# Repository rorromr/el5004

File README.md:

# EL5004: Teleoperación de Go Kart

Desarrollo de un sistema de actuación y teleoperación de un vehículo tipo Go Kart.

Estructura:

```
el5004
|
+-- arduino [Software]
|
+-- doc [Documentación]
|
+-- cad [Archivos CAD]
|
+-- gokart_serial [Interfaz serial con PC]
|
+-- pcb [Diseño PCB]
|
+-- scripts [Scripts de compilación y CI]
```

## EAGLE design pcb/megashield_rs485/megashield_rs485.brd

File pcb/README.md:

# EL5004: Teleoperación de Go Kart

## PCB

El software empleado corresponde [Eagle](http://www.cadsoftusa.com/download-eagle/) (versión >= 7.4).

## Dependencias

* [SparkFun Eagle Libraries](https://github.com/sparkfun/SparkFun-Eagle-Libraries)
* [Librería Eagle Lab. Mecatrónica](https://github.com/mecatronica-fcfm/mecatronica_eagle_lib)

## Componentes principales

* [RS485 Transceiver TI SN75176BP](http://www.ti.com/lit/gpn/sn75176b)

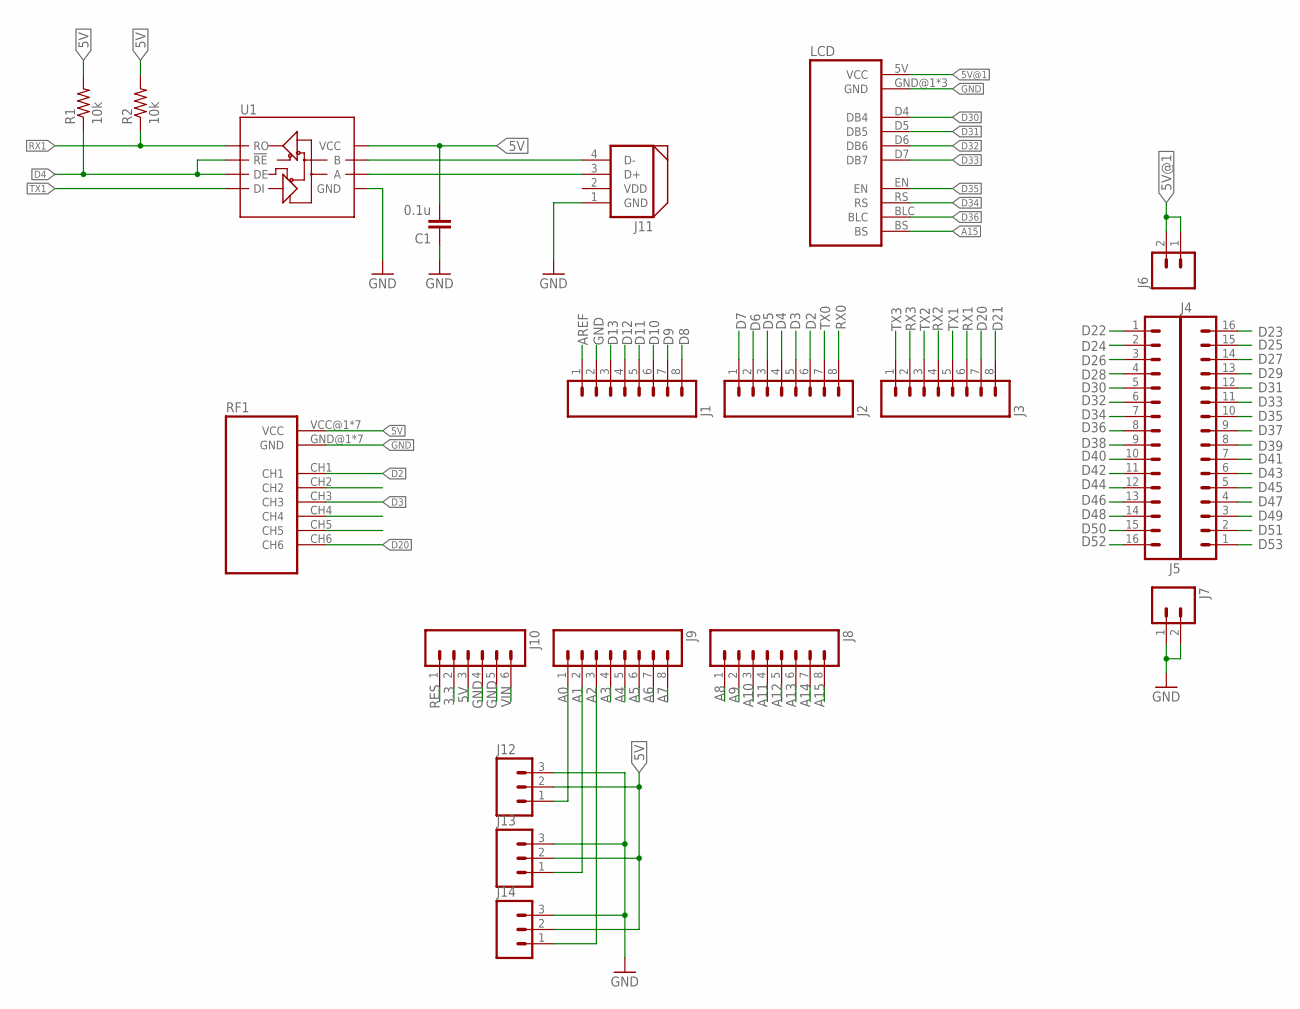
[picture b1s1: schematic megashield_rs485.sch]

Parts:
C1: 0.1u; CAP-PTH-SMALL
J1, J2, J3, J8, J9: M08LONGPADS; 1X08_LONGPADS
J4, J5: M16PTH; 1X16
J6, J7: M02PTH; 1X02
J10: M06LONGPADS; 1X06_LONGPADS
J11: DYNAMIXEL_RS485; DYNAMIXEL_SPOX_04
J12, J13, J14: M03LONGPADS; 1X03_LONGPADS
LCD: LCD_SHIELD
R1, R2: 10k; AXIAL-0.4
RF1: FS_R6B
U1: RS485; DIL08

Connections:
3.3: J10.2
5V: C1.2, J10.3, J12.2, J13.2, J14.2, R1.P$2 (2), R2.P$2 (2), RF1.VCC@1 (VCC), RF1.VCC@2 (VCC), RF1.VCC@3 (VCC), RF1.VCC@4 (VCC), RF1.VCC@5 (VCC), RF1.VCC@6 (VCC), RF1.VCC@7 (VCC), U1.8 (VCC)
5V@1: J6.1, J6.2, LCD.5V (VCC)
A0: J9.1, J12.1
A1: J9.2, J13.1
A2: J9.3, J14.1
A3: J9.4
A4: J9.5
A5: J9.6
A6: J9.7
A7: J9.8
A8: J8.1
A9: J8.2
A10: J8.3
A11: J8.4
A12: J8.5
A13: J8.6
A14: J8.7
A15: J8.8, LCD.BS
AREF: J1.1
D2: J2.6, RF1.CH1
D3: J2.5, RF1.CH3
D4: J2.4, R1.P$1 (1), U1.2 (!RE), U1.3 (DE)
D5: J2.3
D6: J2.2
D7: J2.1
D8: J1.8
D9: J1.7
D10: J1.6
D11: J1.5
D12: J1.4
D13: J1.3
D20: J3.7, RF1.CH6
D21: J3.8
D22: J5.1
D23: J4.16
D24: J5.2
D25: J4.15
D26: J5.3
D27: J4.14
D28: J5.4
D29: J4.13
D30: J5.5, LCD.D4 (DB4)
D31: J4.12, LCD.D5 (DB5)
D32: J5.6, LCD.D6 (DB6)
D33: J4.11, LCD.D7 (DB7)
D34: J5.7, LCD.RS
D35: J4.10, LCD.EN
D36: J5.8, LCD.BLC
D37: J4.9
D38: J5.9
D39: J4.8
D40: J5.10
D41: J4.7
D42: J5.11
D43: J4.6
D44: J5.12
D45: J4.5
D46: J5.13
D47: J4.4
D48: J5.14
D49: J4.3
D50: J5.15
D51: J4.2
D52: J5.16
D53: J4.1
GND: C1.1, J1.2, J7.1, J7.2, J10.4, J10.5, J11.1 (GND), J12.3, J13.3, J14.3, LCD.GND@1 (GND), LCD.GND@2 (GND), LCD.GND@3 (GND), RF1.GND@1 (GND), RF1.GND@2 (GND), RF1.GND@3 (GND), RF1.GND@4 (GND), RF1.GND@5 (GND), RF1.GND@6 (GND), RF1.GND@7 (GND), U1.5 (GND)
unnamed: J11.3 (D+), U1.6 (A)
unnamed: J11.4 (D-), U1.7 (B)
RES: J10.1
RX0: J2.8
RX1: J3.6, R2.P$1 (1), U1.1 (RO)
RX2: J3.4
RX3: J3.2
TX0: J2.7
TX1: J3.5, U1.4 (DI)
TX2: J3.3
TX3: J3.1
VDD: J11.2 (VDD)
VIN: J10.6

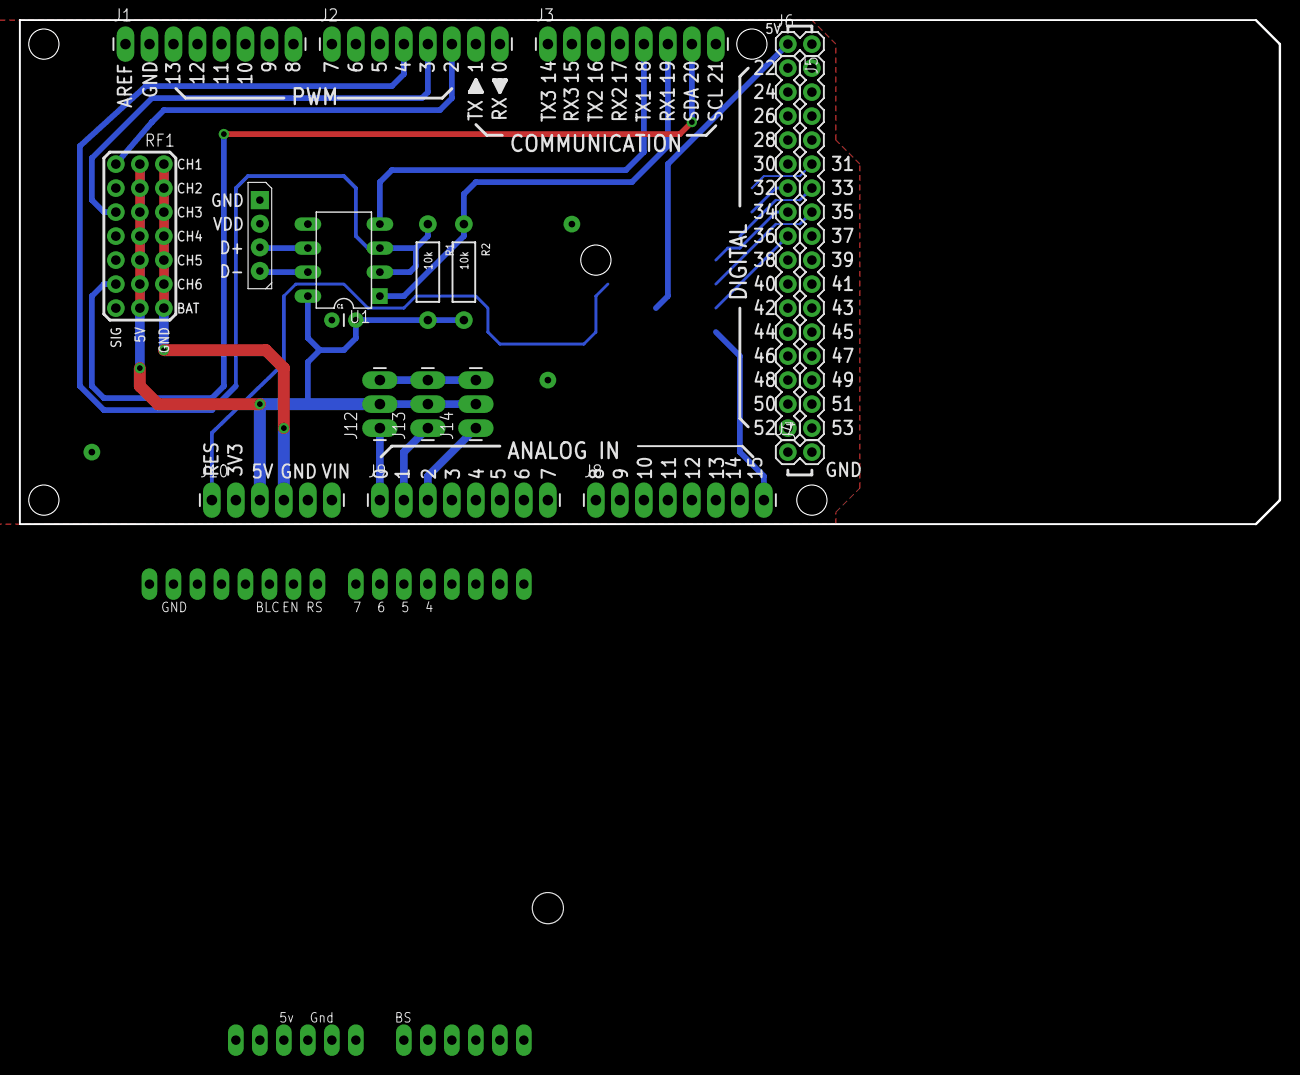
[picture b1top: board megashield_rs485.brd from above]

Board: 2 copper layers, 133.4 x 53.3 mm, 20 parts (0 on the bottom side), 22 nets.

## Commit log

2016-05-25 Estructura de archivos
2016-05-25 Archivo BOM, PCB base para shield
2016-05-25 Metodos Interfaz RF
2016-05-29 Librería Dynamixel
2016-05-29 Interfaz para servos
2016-05-29 Metodos para freno
2016-05-29 Interfaz para actuadores y clase para abstracción del GoKart
2016-05-29 Software como librería de Arduino
2016-05-29 Readmes actualizados
2016-05-31 Manejo de codigos de error en Servo
2016-06-02 GoKart messages with serialization
2016-06-02 Implementacion de RF funcionando, falta completar match para getCommand
2016-06-02 Modificacion de libreria para reemplazar a digitalWrite
2016-06-02 Clase RF Interface implementa metodos de ComInterface
2016-06-02 Fix SetTx and SetRx functions using inline
2016-06-03 March entre valroes RF y enteros para motores en Rf_getCommand
2016-06-06 manejo de clases
2016-06-08 Añadir funciones de debug y configuración de limites
2016-06-08 Fix funciones para set de angulos
2016-06-09 Configuración de angulos máximos y minimos OK
2016-06-09 Fix mensajes de debug y metodos de servomotor
2016-06-09 Mejoras en manejo de errores y configuracion de angulos limites
2016-06-15 Add travis CI config file
2016-06-15 Fix travis config
2016-06-15 Add Travis CI logo
2016-06-15 Prueba de test gokar_integration y probado en el dxl real.
2016-06-16 Mapeo de comando para steering wheel y comandos de velocidad
2016-06-16 Añadir datasheet
2016-06-23 Fix max value for steering wheel command mapping
2016-06-24 Test velocity command in steering wheel
2016-06-24 Emergency state and fix center in steering wheel
2016-06-24 Mejoras en metodos de GoKart, map para freno y metodos init para servos
2016-06-24 Fix println on gokart init method
2016-06-24 Map de acelerador
2016-06-24 Mejoras en scripts de CI
2016-06-24 Fix CI script
2016-06-28 PCB template
2016-06-28 hecho el filtro del rf, falta probar si compila, probar en los pcs de la U
2016-06-28 Add rs485 transceiver
2016-06-28 Add analog inputs
2016-06-28 PCB con elementos para conexion de pantalla
2016-06-30 fix rf_interface mean declaration
2016-06-30 Add scripts readme and update readmes
2016-06-30 Modify pins for PCB
2016-07-01 Serial interface
2016-07-01 Python interface for serial comm
2016-07-02 Serialización de mensaje usando Python
2016-07-03 Basic example using serial interface
2016-07-03 Basic qt graphic interface
2016-07-03 GUI for GoKart
2016-07-06 Add LCD module
2016-07-06 Basic funtions for LCD menu
2016-07-07 Keypad test
2016-07-07 Add init method on GoKart constructor
2016-07-07 LCD screen test
2016-07-07 Nueva lectura de pines RD con interruptores y tambien un enabled del uso del filtro. falta probar
2016-07-07 RF with interrups
2016-07-08 Print on LCD current command
2016-07-08 Motor config using LCD
2016-07-08 LCD test and brake motor limits
2016-07-09 Torque enable funcion
2016-07-09 Fix PCB dimension for better fit on Arduino board
2016-07-13 Add clear command, fix LCD test
2016-07-13 LCD test with print current command
2016-07-13 LCD test with multiple menus
2016-07-13 Implementacion de consistencia de datos y metodo init de RF
2016-07-13 Rama no esta funcinando del todo bien, revisar interrupciones
2016-07-13 Fix throttle
2016-07-14 Add emergency state
2016-07-15 Add realtime plot
2016-07-15 Control de emergencia en apagado y estabilidad de valores
2016-07-15 Fix map for sw actuator
2016-07-18 Keypad class with raising method
2016-07-18 Test rising and falling functions
2016-07-18 Fix servo selected in control panel
2016-07-18 Abstract class for lcd menu
2016-07-18 Logger with different severities
2016-07-18 PCB with LCD
2016-07-19 Add nRF24l01
2016-07-20 PCB v2
2016-07-20 Add PCB v1 and v2
2016-07-20 cambio en flag con overrun, funcionando perfect
2016-07-20 agregar time stamp, funciona bien
2016-07-20 sacar buffer, listo para mezclar con heuristica de pina
2016-07-20 mezcla de ramas mati con pina en master
2016-07-20 Gokart integration with LCD
2016-07-21 Timeour feature, need test!
2016-07-21 cambios en los limites del eoncder del motor direccion
2016-07-21 Function print2
2016-07-21 SW limits
2016-07-23 Command timeout and LCD tested
2016-07-23 Fix test
2016-07-25 Diagram schematic
2016-07-26 Fix default speed
2016-07-28 Add setSpeed method to DxlSErvo
2016-07-28 Add speed menu config
2016-09-02 Preinforme
2016-09-11 CAD link
2016-09-13 Add image
2016-09-13 Center image
